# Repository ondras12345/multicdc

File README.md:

# MultiCDC
This is a simple RP2040-based 6-channel USB to UART converter.

This is my first project using the Zephyr RTOS, so there might be lots of
mistakes. However, it seems to work.

## Operation
The device creates 7 `/dev/ttyACM*` devices when connected to a linux host.
The first 6 are linked to hardware UARTs, and `/dev/ttyACM6` is used for
logging and shell.

The RP2040 only has 2 hardware UARTs. The other 4 channels use the PIOs.

Unfortunately, the `pico-uart-pio` driver doesn't allow changing the baud
rate at runtime. For this reason, baud rates (`current-speed`) for those
channels need to be set in the device tree (`app.overlay`).

Pin map (most of these can be changed arbitrarily):
| pin | function |
|:---:|:--------:|
| P0  | Tx0      |
| P1  | Rx0      |
| P2  | Tx1      |
| P3  | Rx1      |
| P4  | Tx2      |
| P5  | Rx2      |
| P6  | Tx3      |
| P7  | Rx3      |
| P8  | Tx4      |
| P9  | Rx4      |
| P10 | Tx5      |
| P11 | Rx5      |

## Build
```sh
. ~/zephyrproject/.venv/bin/activate
. ~/zephyrproject/zephyr/zephyr-env.sh
west build

# enter bootloader: press BOOT button, press & release RESET, release BOOT
west flash
```

## Udev rules
```sh
sudo tee /etc/udev/rules.d/99-multicdc.rules > /dev/null << "EOF"
SUBSYSTEM=="tty", ENV{ID_VENDOR_ID}=="2fe3", ENV{ID_MODEL_ID}=="6cdc", ENV{ID_USB_INTERFACE_NUM}=="00", SYMLINK+="tty-mcdc0ch0"
SUBSYSTEM=="tty", ENV{ID_VENDOR_ID}=="2fe3", ENV{ID_MODEL_ID}=="6cdc", ENV{ID_USB_INTERFACE_NUM}=="02", SYMLINK+="tty-mcdc0ch1"
SUBSYSTEM=="tty", ENV{ID_VENDOR_ID}=="2fe3", ENV{ID_MODEL_ID}=="6cdc", ENV{ID_USB_INTERFACE_NUM}=="04", SYMLINK+="tty-mcdc0ch2"
SUBSYSTEM=="tty", ENV{ID_VENDOR_ID}=="2fe3", ENV{ID_MODEL_ID}=="6cdc", ENV{ID_USB_INTERFACE_NUM}=="06", SYMLINK+="tty-mcdc0ch3"
SUBSYSTEM=="tty", ENV{ID_VENDOR_ID}=="2fe3", ENV{ID_MODEL_ID}=="6cdc", ENV{ID_USB_INTERFACE_NUM}=="08", SYMLINK+="tty-mcdc0ch4"
SUBSYSTEM=="tty", ENV{ID_VENDOR_ID}=="2fe3", ENV{ID_MODEL_ID}=="6cdc", ENV{ID_USB_INTERFACE_NUM}=="0a", SYMLINK+="tty-mcdc0ch5"
SUBSYSTEM=="tty", ENV{ID_VENDOR_ID}=="2fe3", ENV{ID_MODEL_ID}=="6cdc", ENV{ID_USB_INTERFACE_NUM}=="0c", SYMLINK+="tty-mcdc0shell"
EOF

sudo udevadm control --reload-rules
sudo udevadm trigger
```

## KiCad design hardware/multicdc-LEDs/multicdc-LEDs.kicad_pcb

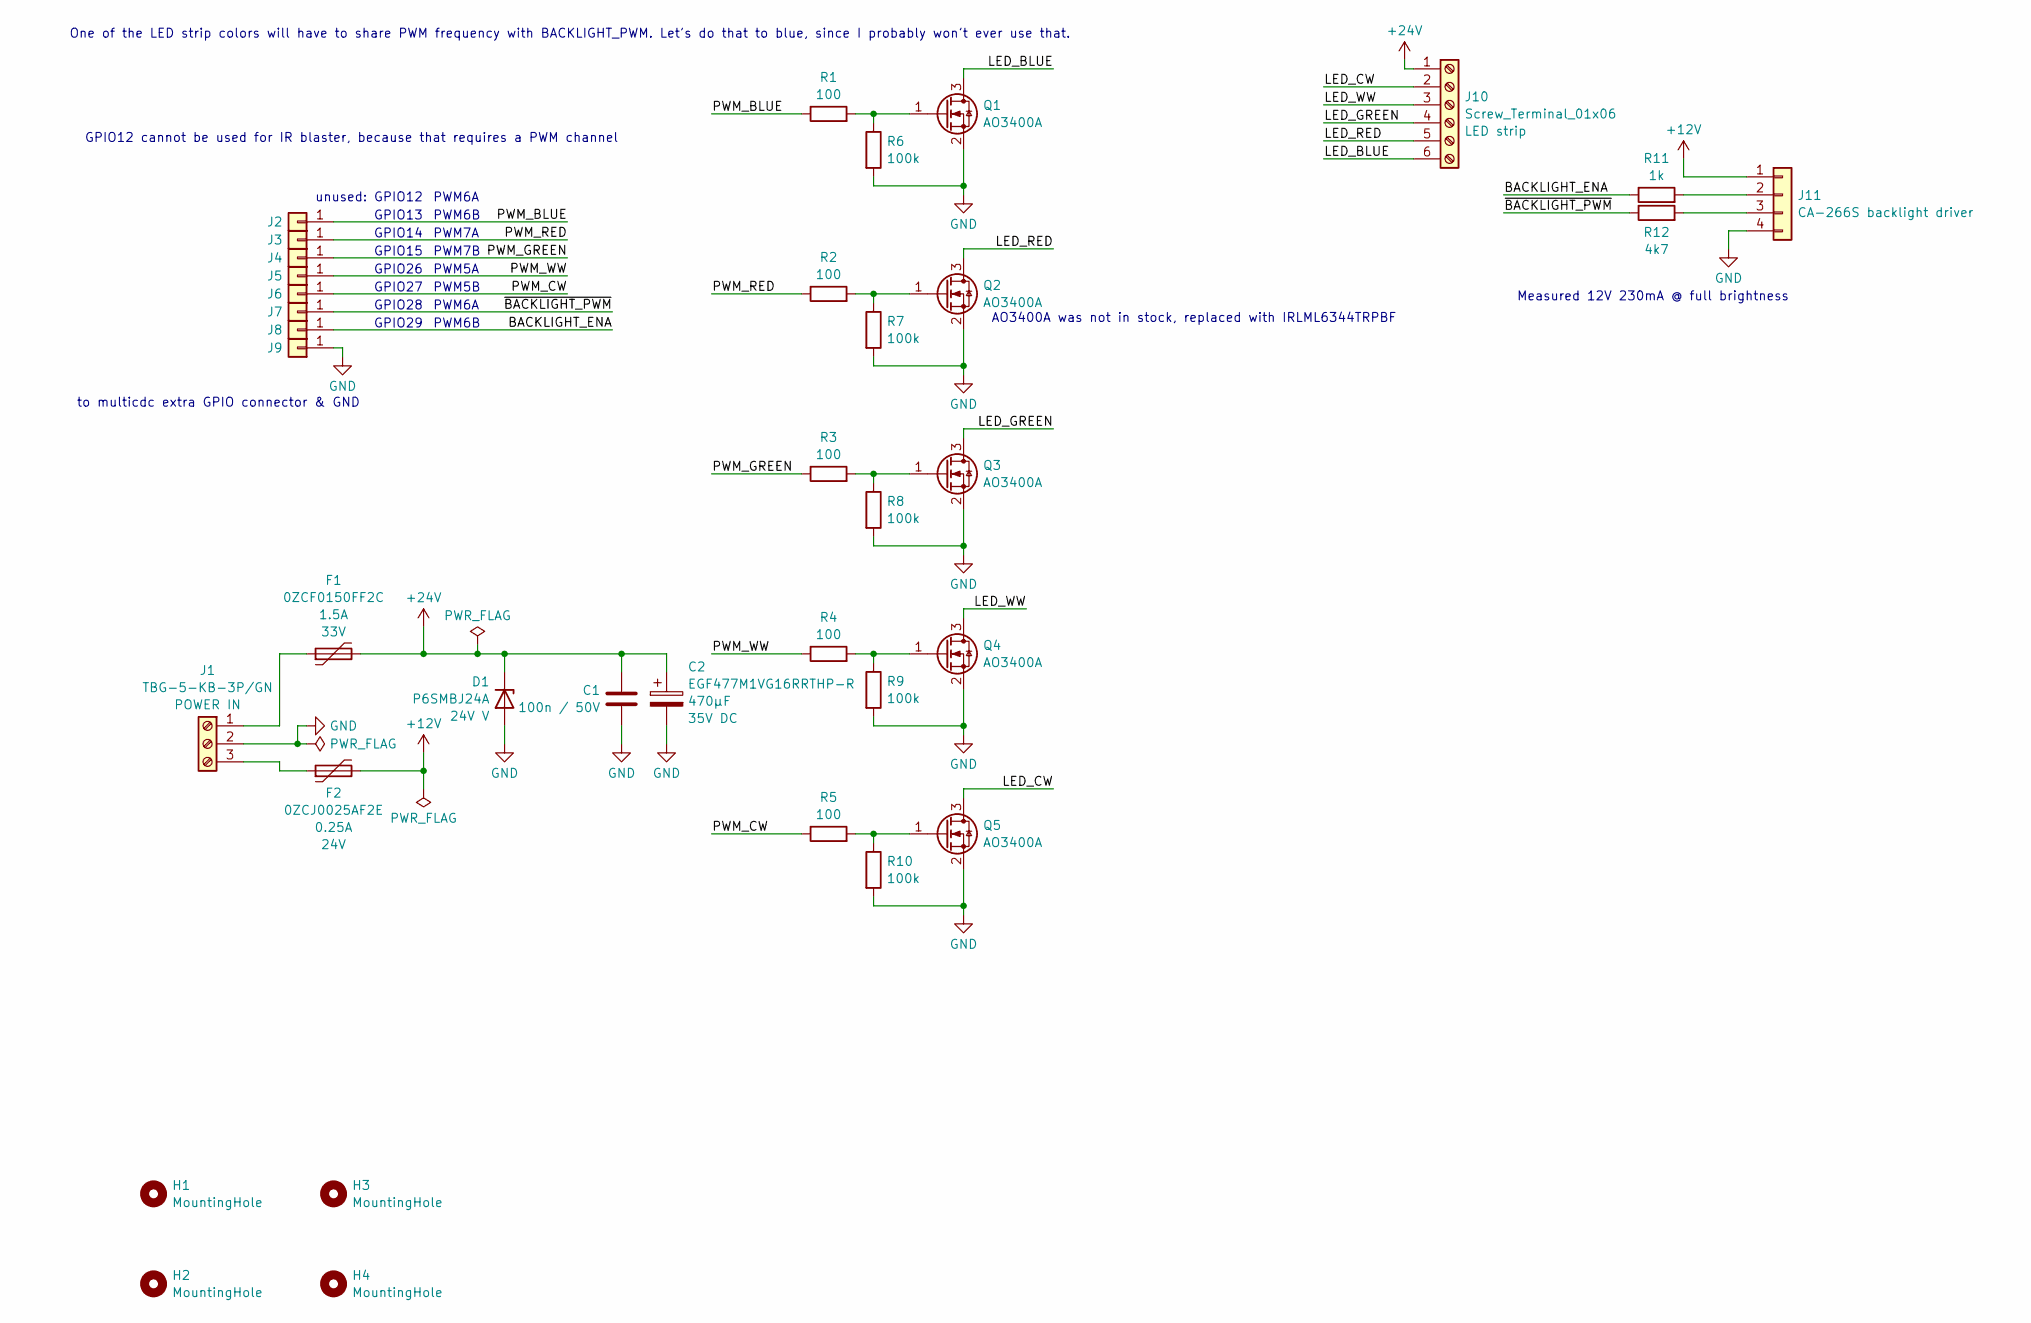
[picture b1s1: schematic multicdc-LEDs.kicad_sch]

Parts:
C1: 100n / 50V; C_1206_3216Metric_Pad1.33x1.80mm_HandSolder
C2: EGF477M1VG16RRTHP-R; CP_Radial_D10.0mm_P5.00mm; Tolerance 20% %; Rated Voltage 35V DC
D1: P6SMBJ24A; D_SMB_Handsoldering; Forward Voltage 26.7...29.6V; Standoff Voltage 24V V
F1: 0ZCF0150FF2C; Fuse_2920_7451Metric_Pad2.10x5.45mm_HandSolder; Rated Voltage 33V
F2: 0ZCJ0025AF2E; Fuse_1206_3216Metric_Pad1.42x1.75mm_HandSolder; Rated Voltage 24V
H1, H2, H3, H4: MountingHole; MountingHole_3.2mm_M3
J1: TBG-5-KB-3P/GN; TBG-5-KB-3P_1x03_P5.08mm_Horizontal; Rated Voltage 0.3kV
J2, J3, J4, J5, J6, J7, J8, J9: Conn_01x01; SolderWire-0.25sqmm_1x01_D0.65mm_OD1.7mm_Relief
J10: Screw_Terminal_01x06; TerminalBlock_Xinya_XY301VA-5.00-6P_1x06_P5.00mm_Horizontal
J11: soldered wires; SolderWire-0.25sqmm_1x04_P4.2mm_D0.65mm_OD1.7mm_Relief
Q1, Q2, Q3, Q4, Q5: AO3400A; SOT-23; Rated Voltage 30V
R1, R2, R3, R4, R5: 100; R_0805_2012Metric_Pad1.20x1.40mm_HandSolder
R6, R7, R8, R9, R10: 100k; R_0805_2012Metric_Pad1.20x1.40mm_HandSolder
R11: 1k; R_0805_2012Metric_Pad1.20x1.40mm_HandSolder
R12: 4k7; R_0805_2012Metric_Pad1.20x1.40mm_HandSolder

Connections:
+12V: F2.2, J11.1
+24V: C1.1, C2.1, D1.1 (K), F1.2, J10.1
/BACKLIGHT_ENA: J8.1, R11.1
/LED_BLUE: J10.6, Q1.3 (D)
/LED_CW: J10.2, Q5.3 (D)
/LED_GREEN: J10.4, Q3.3 (D)
/LED_RED: J10.5, Q2.3 (D)
/LED_WW: J10.3, Q4.3 (D)
/PWM_BLUE: J2.1, R1.1
/PWM_CW: J6.1, R5.1
/PWM_GREEN: J4.1, R3.1
/PWM_RED: J3.1, R2.1
/PWM_WW: J5.1, R4.1
/~BACKLIGHT_PWM: J7.1, R12.1
GND: C1.2, C2.2, D1.2 (A), J1.2, J9.1, J11.4, Q1.2 (S), Q2.2 (S), Q3.2 (S), Q4.2 (S), Q5.2 (S), R6.2, R7.2, R8.2, R9.2, R10.2
unnamed: F1.1, J1.1
unnamed: F2.1, J1.3
unnamed: J11.2, R11.2
unnamed: J11.3, R12.2
unnamed: Q1.1 (G), R1.2, R6.1
unnamed: Q2.1 (G), R2.2, R7.1
unnamed: Q3.1 (G), R3.2, R8.1
unnamed: Q4.1 (G), R4.2, R9.1
unnamed: Q5.1 (G), R5.2, R10.1

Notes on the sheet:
Measured 12V 230mA @ full brightness
GPIO15
GPIO27
GPIO29
GPIO26
unused: GPIO12
PWM5B
PWM6B
PWM7B
PWM5A
GPIO13
AO3400A was not in stock, replaced with IRLML6344TRPBF
One of the LED strip colors will have to share PWM frequency with BACKLIGHT_PWM. Let's do that to blue, since I probably won't ever use that.
to multicdc extra GPIO connector & GND
PWM7A
GPIO14
PWM6A
GPIO28
GPIO12 cannot be used for IR blaster, because that requires a PWM channel

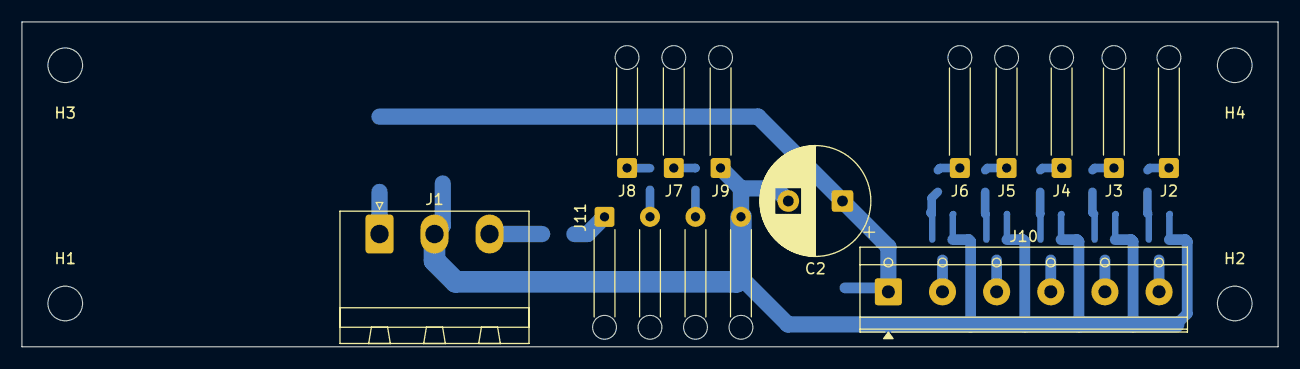
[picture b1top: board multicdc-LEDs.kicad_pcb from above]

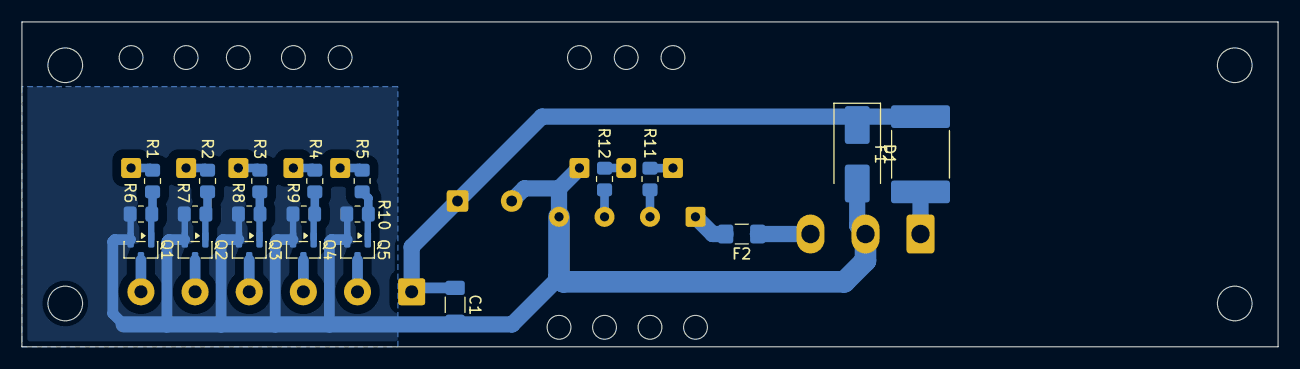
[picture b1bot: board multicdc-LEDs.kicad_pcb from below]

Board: 2 copper layers, 116.0 x 30.0 mm, 37 parts (21 on the bottom side), 24 nets.

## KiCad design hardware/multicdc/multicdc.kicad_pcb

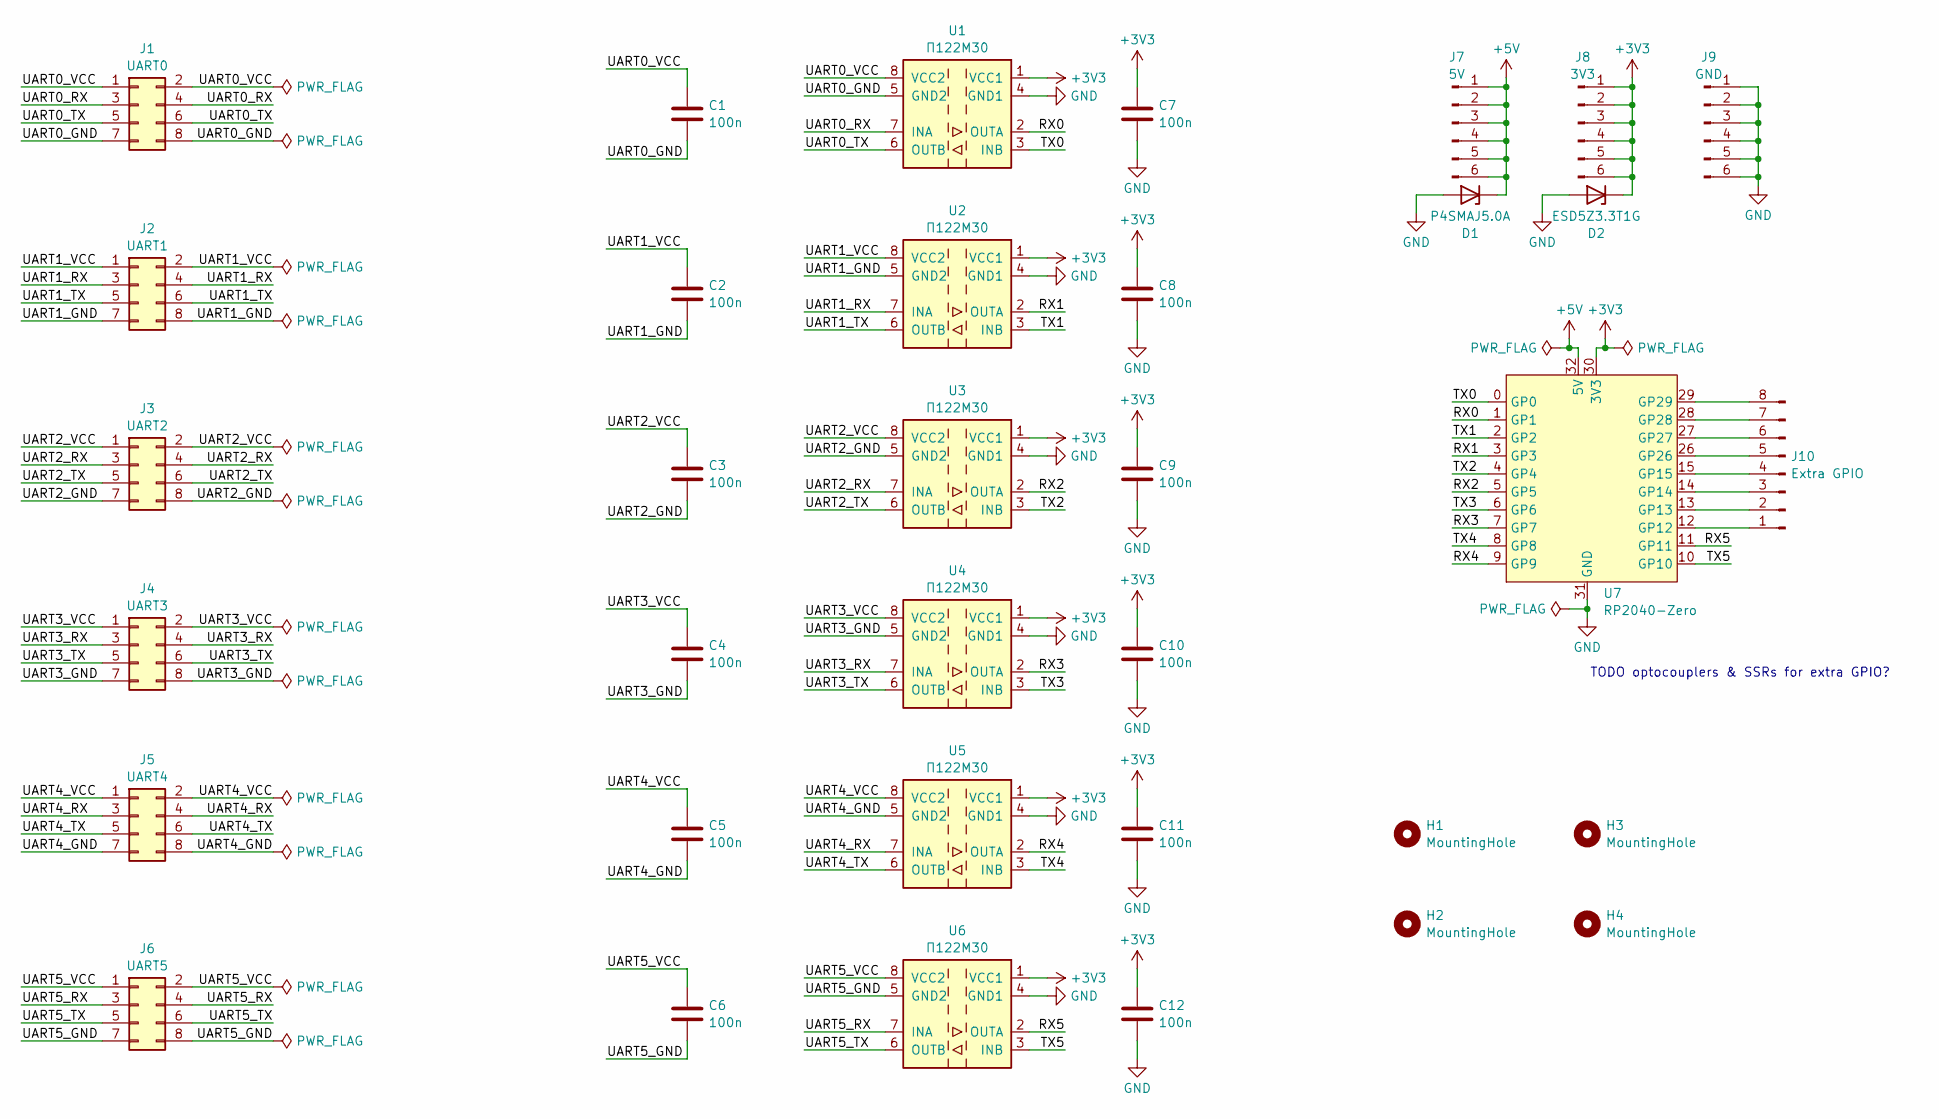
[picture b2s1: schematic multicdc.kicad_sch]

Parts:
C1, C2, C3, C4, C5, C6, C7, C8, C9, C10, C11, C12: 100n; C_0805_2012Metric_Pad1.18x1.45mm_HandSolder
D1: P4SMAJ5.0A; D_SMA_Handsoldering; Forward Voltage 6.4...7V; Standoff Voltage 5V
D2: ESD5Z3.3T1G; D_SOD-523; Forward Voltage 5V; Standoff Voltage 3.3V
H1, H2, H3, H4: MountingHole; MountingHole_3.2mm_M3
J1, J2, J3, J4, J5, J6: Conn_02x04_Odd_Even; PinHeader_2x04_P2.54mm_Vertical
J7, J8, J9: Conn_01x06_Pin; PinHeader_1x06_P2.54mm_Vertical
J10: Conn_01x08_Pin; PinHeader_1x08_P2.54mm_Vertical
U1, U2, U3, U4, U5, U6: Π122M30; SOIC-8_3.9x4.9mm_P1.27mm; Supply Voltage 3...5.5V DC
U7: RP2040-Zero

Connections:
+3V3: C7.1, C8.1, C9.1, C10.1, C11.1, C12.1, D2.1 (K), J8.1, J8.2, J8.3, J8.4, J8.5, J8.6, U1.1 (VCC1), U2.1 (VCC1), U3.1 (VCC1), U4.1 (VCC1), U5.1 (VCC1), U6.1 (VCC1), U7.30 (3V3)
+5V: D1.1 (K), J7.1, J7.2, J7.3, J7.4, J7.5, J7.6, U7.32 (5V)
/RX0: U1.2 (OUTA), U7.1 (GP1)
/RX1: U2.2 (OUTA), U7.3 (GP3)
/RX2: U3.2 (OUTA), U7.5 (GP5)
/RX3: U4.2 (OUTA), U7.7 (GP7)
/RX4: U5.2 (OUTA), U7.9 (GP9)
/RX5: U6.2 (OUTA), U7.11 (GP11)
/TX0: U1.3 (INB), U7.0 (GP0)
/TX1: U2.3 (INB), U7.2 (GP2)
/TX2: U3.3 (INB), U7.4 (GP4)
/TX3: U4.3 (INB), U7.6 (GP6)
/TX4: U5.3 (INB), U7.8 (GP8)
/TX5: U6.3 (INB), U7.10 (GP10)
/UART0_GND: C1.2, J1.7, J1.8, U1.5 (GND2)
/UART0_RX: J1.3, J1.4, U1.7 (INA)
/UART0_TX: J1.5, J1.6, U1.6 (OUTB)
/UART0_VCC: C1.1, J1.1, J1.2, U1.8 (VCC2)
/UART1_GND: C2.2, J2.7, J2.8, U2.5 (GND2)
/UART1_RX: J2.3, J2.4, U2.7 (INA)
/UART1_TX: J2.5, J2.6, U2.6 (OUTB)
/UART1_VCC: C2.1, J2.1, J2.2, U2.8 (VCC2)
/UART2_GND: C3.2, J3.7, J3.8, U3.5 (GND2)
/UART2_RX: J3.3, J3.4, U3.7 (INA)
/UART2_TX: J3.5, J3.6, U3.6 (OUTB)
/UART2_VCC: C3.1, J3.1, J3.2, U3.8 (VCC2)
/UART3_GND: C4.2, J4.7, J4.8, U4.5 (GND2)
/UART3_RX: J4.3, J4.4, U4.7 (INA)
/UART3_TX: J4.5, J4.6, U4.6 (OUTB)
/UART3_VCC: C4.1, J4.1, J4.2, U4.8 (VCC2)
/UART4_GND: C5.2, J5.7, J5.8, U5.5 (GND2)
/UART4_RX: J5.3, J5.4, U5.7 (INA)
/UART4_TX: J5.5, J5.6, U5.6 (OUTB)
/UART4_VCC: C5.1, J5.1, J5.2, U5.8 (VCC2)
/UART5_GND: C6.2, J6.7, J6.8, U6.5 (GND2)
/UART5_RX: J6.3, J6.4, U6.7 (INA)
/UART5_TX: J6.5, J6.6, U6.6 (OUTB)
/UART5_VCC: C6.1, J6.1, J6.2, U6.8 (VCC2)
GND: C7.2, C8.2, C9.2, C10.2, C11.2, C12.2, D1.2 (A), D2.2 (A), J9.1, J9.2, J9.3, J9.4, J9.5, J9.6, U1.4 (GND1), U2.4 (GND1), U3.4 (GND1), U4.4 (GND1), U5.4 (GND1), U6.4 (GND1), U7.31 (GND)
unnamed: J10.1, U7.12 (GP12)
unnamed: J10.2, U7.13 (GP13)
unnamed: J10.3, U7.14 (GP14)
unnamed: J10.4, U7.15 (GP15)
unnamed: J10.5, U7.26 (GP26)
unnamed: J10.6, U7.27 (GP27)
unnamed: J10.7, U7.28 (GP28)
unnamed: J10.8, U7.29 (GP29)

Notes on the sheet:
TODO optocouplers & SSRs for extra GPIO?

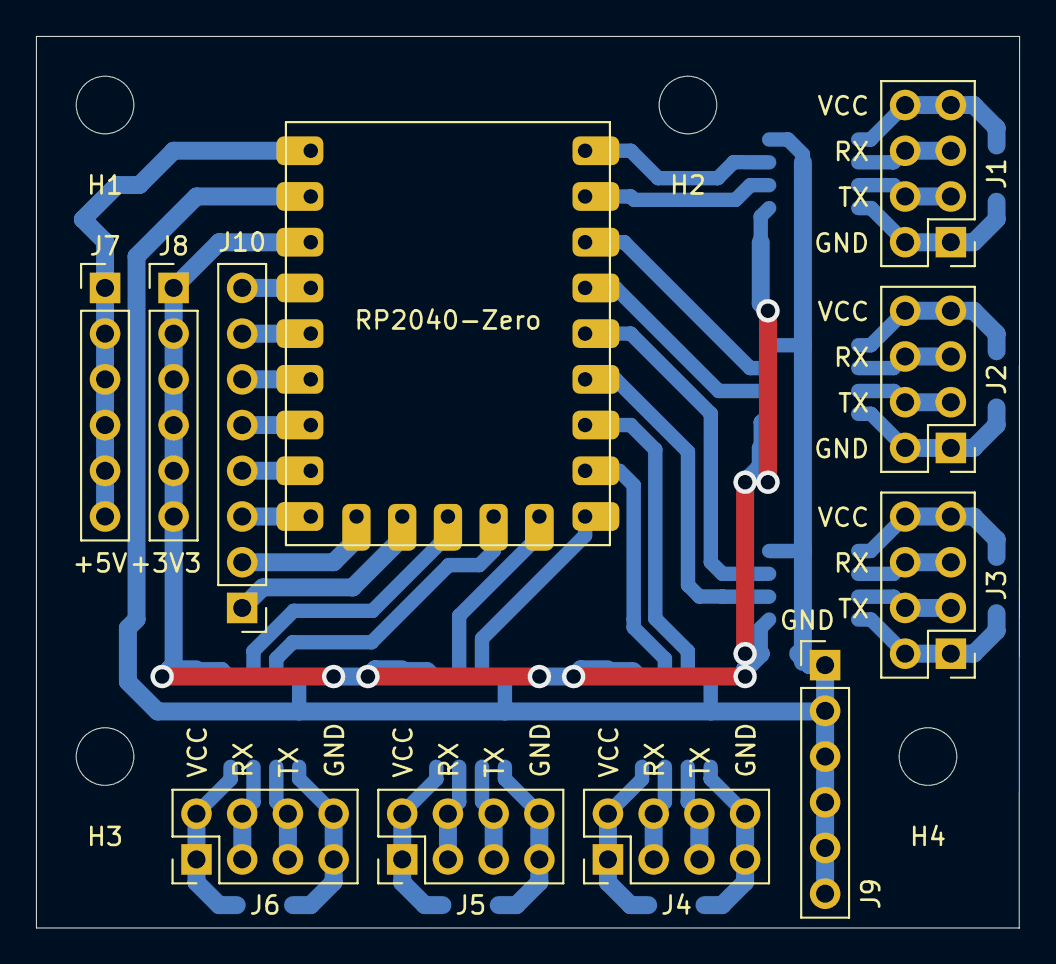
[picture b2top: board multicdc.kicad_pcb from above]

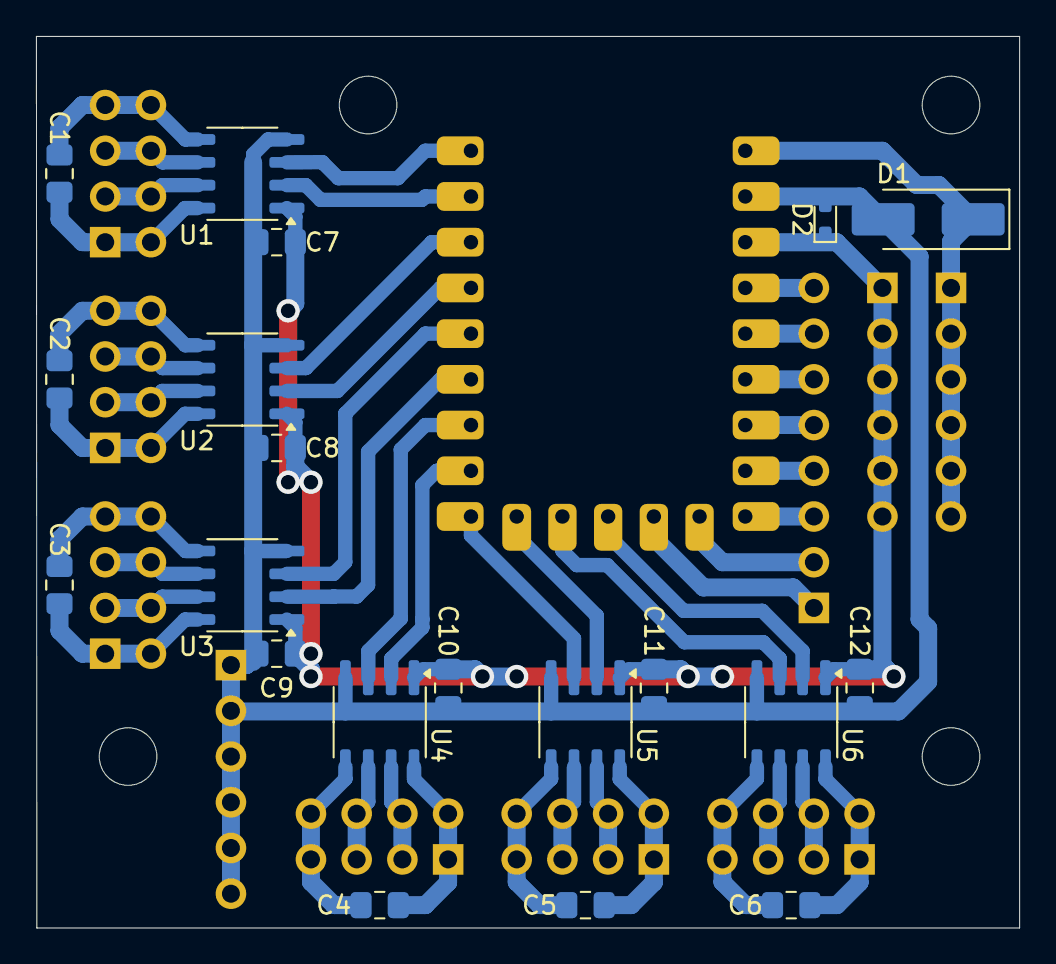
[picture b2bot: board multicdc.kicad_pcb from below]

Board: 2 copper layers, 54.6 x 49.5 mm, 35 parts (20 on the bottom side), 47 nets.

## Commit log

2025-03-09 Add project files
    This seems to be working.
2025-03-09 Remove dependency on zephyr samples
2025-03-09 Improve documentation
2025-03-09 Add LICENSE
2025-03-12 Fix typo in README
2025-03-12 Improve pin map
2025-03-12 Fix typo in Rx5 pin name in README
2025-03-14 Add hardware designs
2025-03-15 Finish hardware designs
2025-03-20 Fix Kconfig copied from sample
    As far as I can tell, this didn't actually cause any trouble.
2025-08-08 Set shell prompt
2025-08-08 Add note to PCB
2025-08-10 Set baud rates
2025-08-10 Add udev rules to README
2025-10-27 Add PCB renders to README
2026-02-11 Add multicdc-LEDs PCB design
2026-02-11 Implement LED control
2026-02-11 Improve LED PWM resolution
2026-02-13 Remove commented out modbus code
2026-02-13 Add tools/leds_gamma.py
2026-02-13 Implement MQTT LED control
2026-02-21 Fix LEDs GPIO control
2026-02-21 Fix backlight ON command
2026-02-21 Fix flake8 warnings
2026-02-21 Report color temperatures in discovery message
2026-02-24 Report rgbcct brightness to mqtt
2026-03-03 Retain light status MQTT messages
2026-03-17 Increase default RGBCCT brightness
